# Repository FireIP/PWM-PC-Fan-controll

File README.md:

# PWM-PC-Fan-controll
An Arduino project for controlling 3 PC fans to cool a shelf of PCs.

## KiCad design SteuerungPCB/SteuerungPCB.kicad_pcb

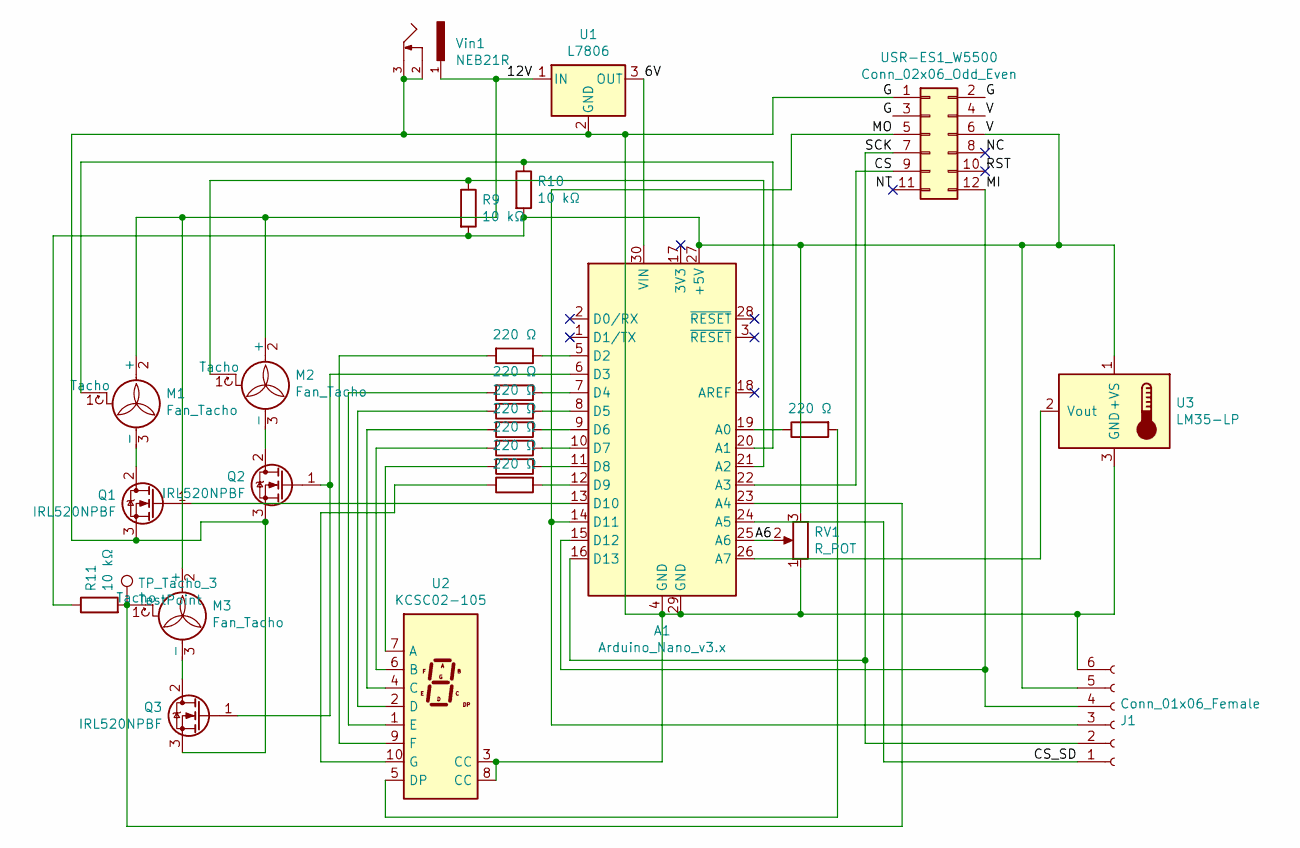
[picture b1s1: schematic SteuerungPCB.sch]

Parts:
A1: Arduino_Nano_v3.x; Arduino_Nano
J1: Conn_01x06_Female; PinSocket_1x06_P2.54mm_Horizontal
M1, M2, M3: Fan_Tacho; FanPinHeader_1x03_P2.54mm_Vertical
Q1, Q2, Q3: IRL520NPBF; TO-220-3_Horizontal_TabUp_SK_95_25
R1, R2, R3, R4, R5, R6, R7, R8: 220 Ω; R_0805_2012Metric
R9, R10, R11: 10 kΩ; R_0805_2012Metric
RV1: R_POT; Potentiometer_Alps_RK09L_Double_Horizontal_Edge_mount
TP_Tacho_3: TestPoint; TestPoint_THTPad_2.0x2.0mm_Drill1.0mm
U1: L7806; TO-220-3_Horizontal_TabUp_SK_95_25
U2: KCSC02-105; Sx39-1xxxxx
U3: LM35-LP; PinSocket_1x03_P2.54mm_Horizontal
USR-ES1_W5500: Conn_02x06_Odd_Even; USR-ES1_W5500_v2
Vin1: NEB21R; MPN NEB 21 R

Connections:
/6V: A1.30 (VIN), U1.3 (OUT)
/12V: M1.2 (+), M2.2 (+), M3.2 (+), U1.1 (IN), Vin1.1
/A6: A1.25 (A6), RV1.2
/CS: A1.22 (A3), USR-ES1_W5500.9
/CS_SD: A1.24 (A5), J1.1
/G: A1.4 (GND), A1.29 (GND), J1.6, Q1.3 (S), Q2.3 (S), Q3.3 (S), RV1.1, U1.2 (GND), U2.3 (CC), U2.8 (CC), U3.3 (GND), USR-ES1_W5500.1, USR-ES1_W5500.2, USR-ES1_W5500.3, Vin1.2, Vin1.3
/MI: A1.15 (D12), J1.4, USR-ES1_W5500.12
/MO: A1.14 (D11), J1.3, USR-ES1_W5500.5
/NC: USR-ES1_W5500.8
/NT: USR-ES1_W5500.11
/RST: USR-ES1_W5500.10
/SCK: A1.16 (D13), J1.2, USR-ES1_W5500.7
/V: A1.27 (+5V), J1.5, R9.2, R10.2, R11.1, RV1.3, U3.1 (+VS), USR-ES1_W5500.4, USR-ES1_W5500.6
unnamed: A1.5 (D2), R1.1
unnamed: A1.6 (D3), Q2.1 (G), Q3.1 (G)
unnamed: A1.7 (D4), R3.1
unnamed: A1.8 (D5), R4.1
unnamed: A1.9 (D6), R5.2
unnamed: A1.10 (D7), R6.2
unnamed: A1.11 (D8), R7.2
unnamed: A1.12 (D9), R2.2
unnamed: A1.13 (D10), Q1.1 (G)
unnamed: A1.19 (A0), R8.1
unnamed: A1.20 (A1), M1.1 (Tacho), R10.1
unnamed: A1.21 (A2), M2.1 (Tacho), R9.1
unnamed: A1.23 (A4), M3.1 (Tacho), R11.2, TP_Tacho_3.1
unnamed: A1.26 (A7), U3.2 (Vout)
unnamed: M1.3 (-), Q1.2 (D)
unnamed: M2.3 (-), Q2.2 (D)
unnamed: M3.3 (-), Q3.2 (D)
unnamed: R1.2, U2.9 (F)
unnamed: R2.1, U2.10 (G)
unnamed: R3.2, U2.1 (E)
unnamed: R4.2, U2.2 (D)
unnamed: R5.1, U2.4 (C)
unnamed: R6.1, U2.6 (B)
unnamed: R7.1, U2.7 (A)
unnamed: R8.2, U2.5 (DP)

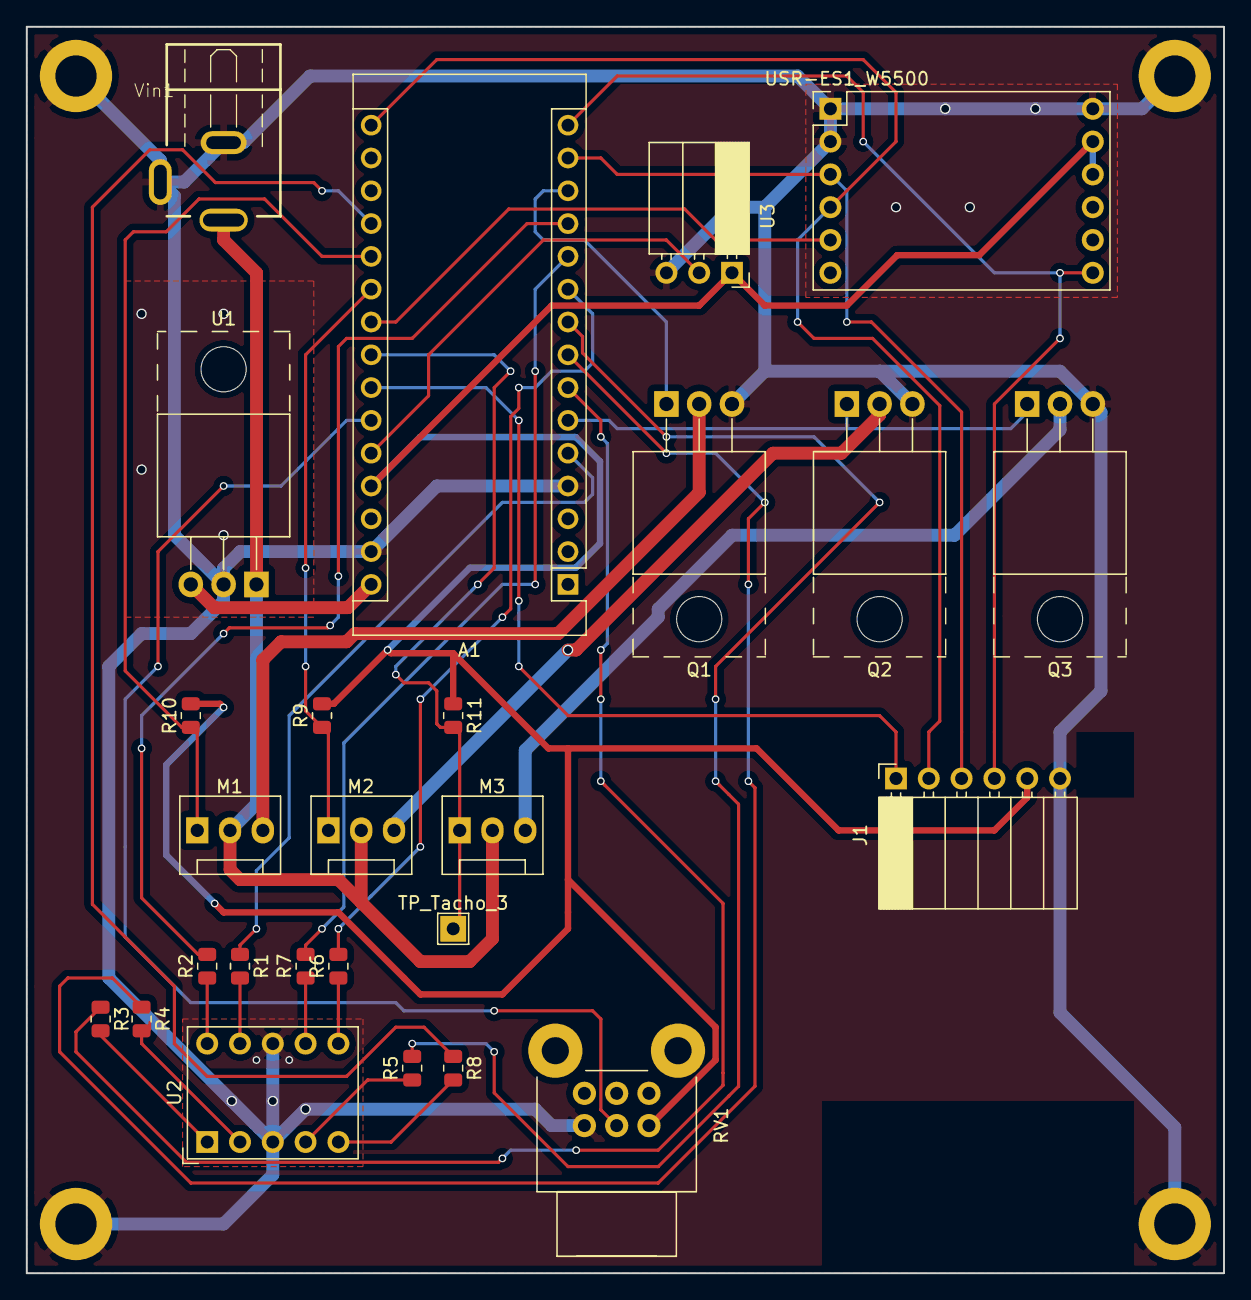
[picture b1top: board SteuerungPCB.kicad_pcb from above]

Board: 2 copper layers, 92.7 x 96.5 mm, 26 parts (0 on the bottom side), 35 nets.

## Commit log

2022-05-01 Upload to Git
2024-01-30 init rewrite: cleanup versions minor improvements before actual rewrite
2024-01-30 rewrite: shorten HTML placeholders #i Please enter the commit message for your changes. Lines starting # with '#' will be ignored, and an empty message aborts the commit. # # On branch rewrite # Your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
